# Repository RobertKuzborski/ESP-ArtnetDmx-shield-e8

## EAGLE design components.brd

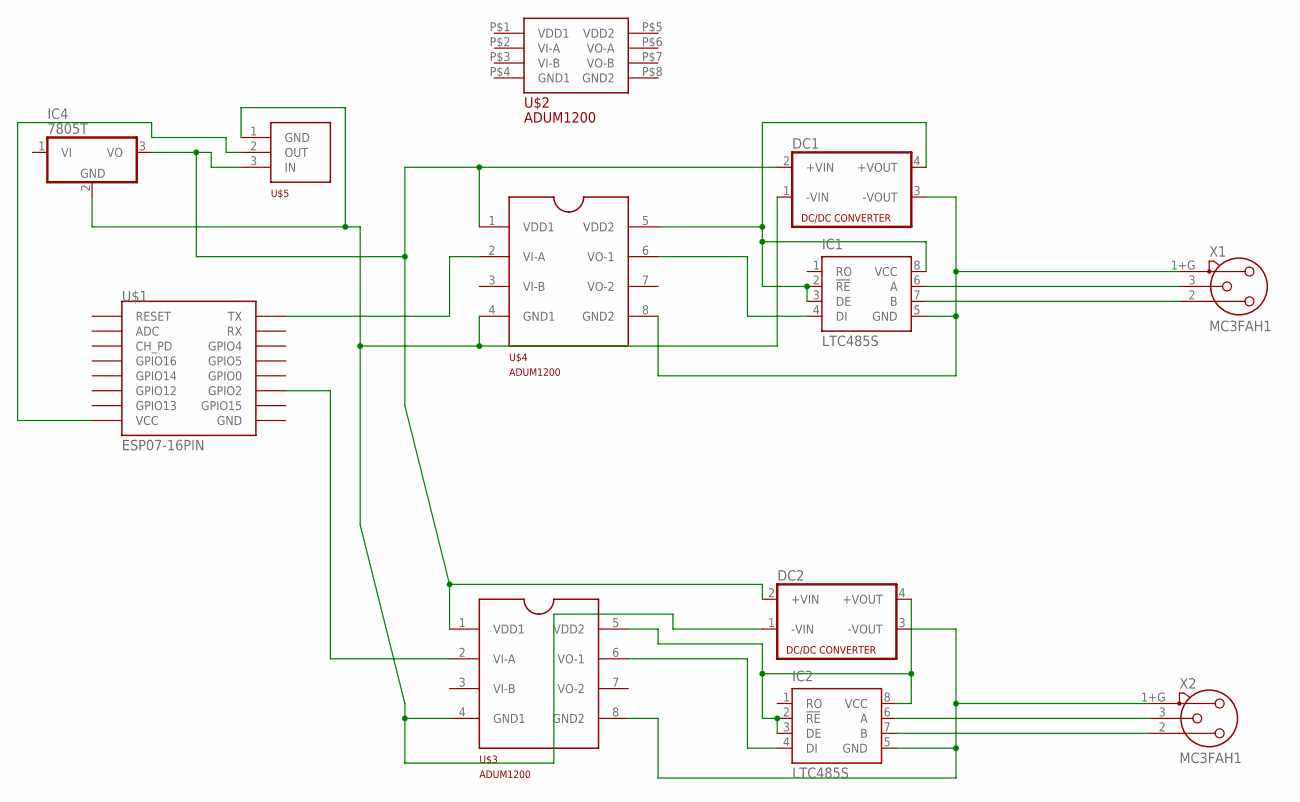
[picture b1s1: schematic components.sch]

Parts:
DC1, DC2: NME
IC1, IC2: LTC485S; SOIC8
IC4: 7805T; TO220H
U$1: ESP07-16PIN
U$2: ADUM1200SO8; SO8
U$3, U$4: ADUM1200; SO8
U$5: AMS1117; SOT223
X1, X2: MC3FAH1; NC3FAH1

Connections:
unnamed: DC2.3 (-VOUT), IC2.5 (GND), U$3.8 (GND2), X2.1+G (1)
unnamed: DC1.3 (-VOUT), IC1.5 (GND), U$4.8 (GND2), X1.1+G (1)
unnamed: IC2.7 (B), X2.2
unnamed: IC2.6 (A), X2.3
unnamed: DC2.4 (+VOUT), IC2.2 (!RE), IC2.3 (DE), IC2.8 (VCC), U$3.5 (VDD2)
unnamed: DC1.4 (+VOUT), IC1.2 (!RE), IC1.3 (DE), IC1.8 (VCC), U$4.5 (VDD2)
unnamed: IC2.4 (DI), U$3.6 (VO-1)
unnamed: DC1.2 (+VIN), DC2.2 (+VIN), IC4.3 (VO), U$3.1 (VDD1), U$4.1 (VDD1), U$5.3 (IN)
unnamed: DC1.1 (-VIN), DC2.1 (-VIN), IC4.2 (GND), U$3.4 (GND1), U$4.4 (GND1), U$5.1 (GND)
unnamed: U$1.VCC, U$5.2 (OUT)
unnamed: U$1.GPIO2, U$3.2 (VI-A)
unnamed: U$1.TX, U$4.2 (VI-A)
unnamed: IC1.4 (DI), U$4.6 (VO-1)
unnamed: IC1.7 (B), X1.2
unnamed: IC1.6 (A), X1.3

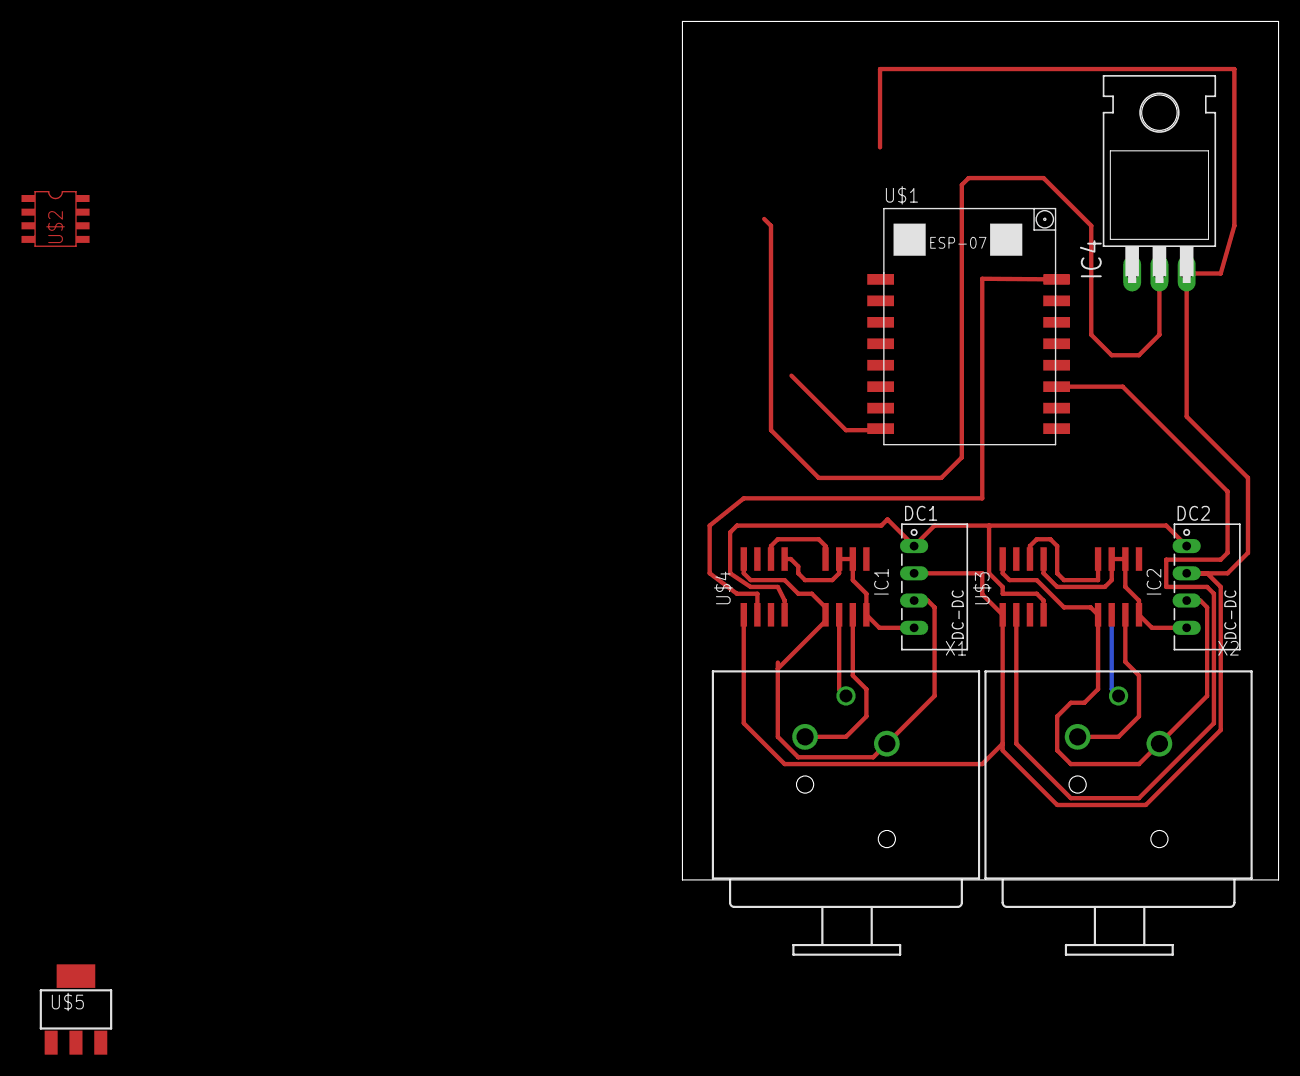
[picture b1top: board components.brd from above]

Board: 2 copper layers, 55.5 x 80.0 mm, 12 parts (0 on the bottom side), 15 nets.
